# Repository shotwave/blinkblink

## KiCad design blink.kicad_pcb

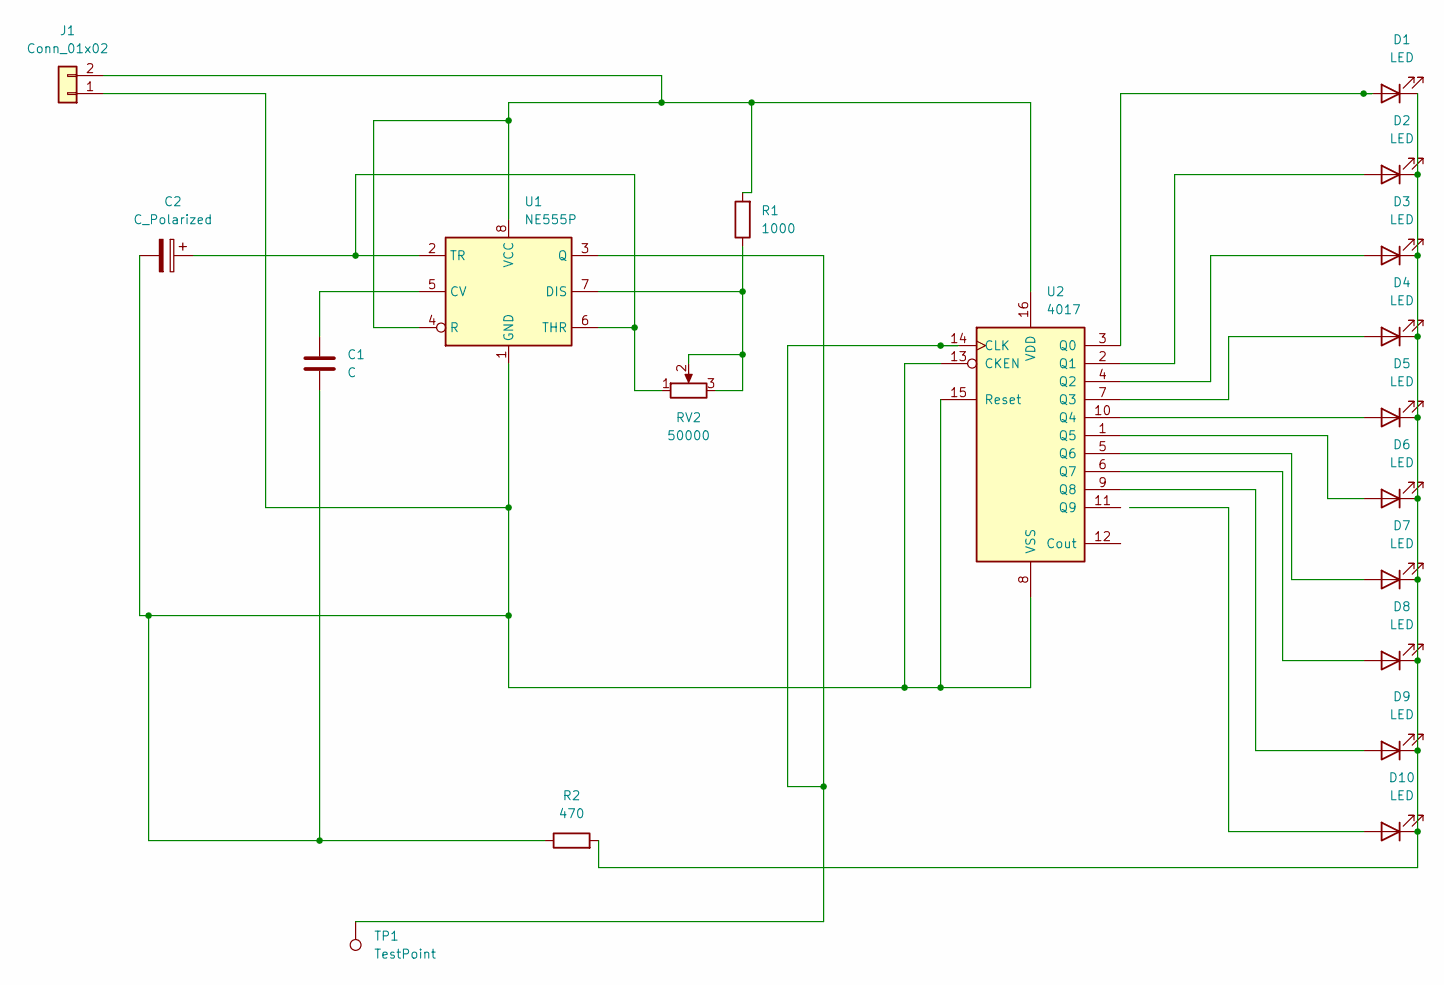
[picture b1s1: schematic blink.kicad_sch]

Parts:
C1: C; CP_Radial_D5.0mm_P2.50mm
C2: C_Polarized; C_Disc_D3.0mm_W2.0mm_P2.50mm
D1, D2, D3, D4, D5, D6, D7, D8, D9, D10: LED; LED_0805_2012Metric
J1: Conn_01x02; PinHeader_1x02_P2.54mm_Vertical
R1: 1000; R_Axial_DIN0207_L6.3mm_D2.5mm_P7.62mm_Horizontal
R2: 470; R_Axial_DIN0207_L6.3mm_D2.5mm_P7.62mm_Horizontal
RV2: 50000; Potentiometer_Bourns_3386P_Vertical
TP1: TestPoint; TestPoint_Pad_D1.5mm
U1: NE555P; DIP-8_W7.62mm
U2: 4017; DIP-16_W7.62mm

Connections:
unnamed: D1.2 (A), U2.3 (Q0)
unnamed: D1.1 (K), D2.1 (K), D3.1 (K), D4.1 (K), D5.1 (K), D6.1 (K), D7.1 (K), D8.1 (K), D9.1 (K), D10.1 (K), R2.2
unnamed: D2.2 (A), U2.2 (Q1)
unnamed: D3.2 (A), U2.4 (Q2)
unnamed: D4.2 (A), U2.7 (Q3)
unnamed: D5.2 (A), U2.10 (Q4)
unnamed: D6.2 (A), U2.1 (Q5)
unnamed: D7.2 (A), U2.5 (Q6)
unnamed: D8.2 (A), U2.6 (Q7)
unnamed: D9.2 (A), U2.9 (Q8)
unnamed: C1.2, C2.2, J1.1, R2.1, U1.1 (GND), U2.8 (VSS), U2.13 (CKEN), U2.15 (Reset)
unnamed: J1.2, R1.2, U1.4 (R), U1.8 (VCC), U2.16 (VDD)
unnamed: C1.1, U1.5 (CV)
unnamed: R1.1, RV2.2, RV2.3, U1.7 (DIS)
unnamed: TP1.1, U1.3 (Q), U2.14 (CLK)
unnamed: C2.1, RV2.1, U1.2 (TR), U1.6 (THR)

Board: 2 copper layers, 19 parts (0 on the bottom side), 16 nets, no tracks yet.

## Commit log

2025-11-02 Done
